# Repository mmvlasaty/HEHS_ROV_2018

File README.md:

# HEHS_ROV_2018

Control system repository for the HEHS 2018 MATE ROV competition team.

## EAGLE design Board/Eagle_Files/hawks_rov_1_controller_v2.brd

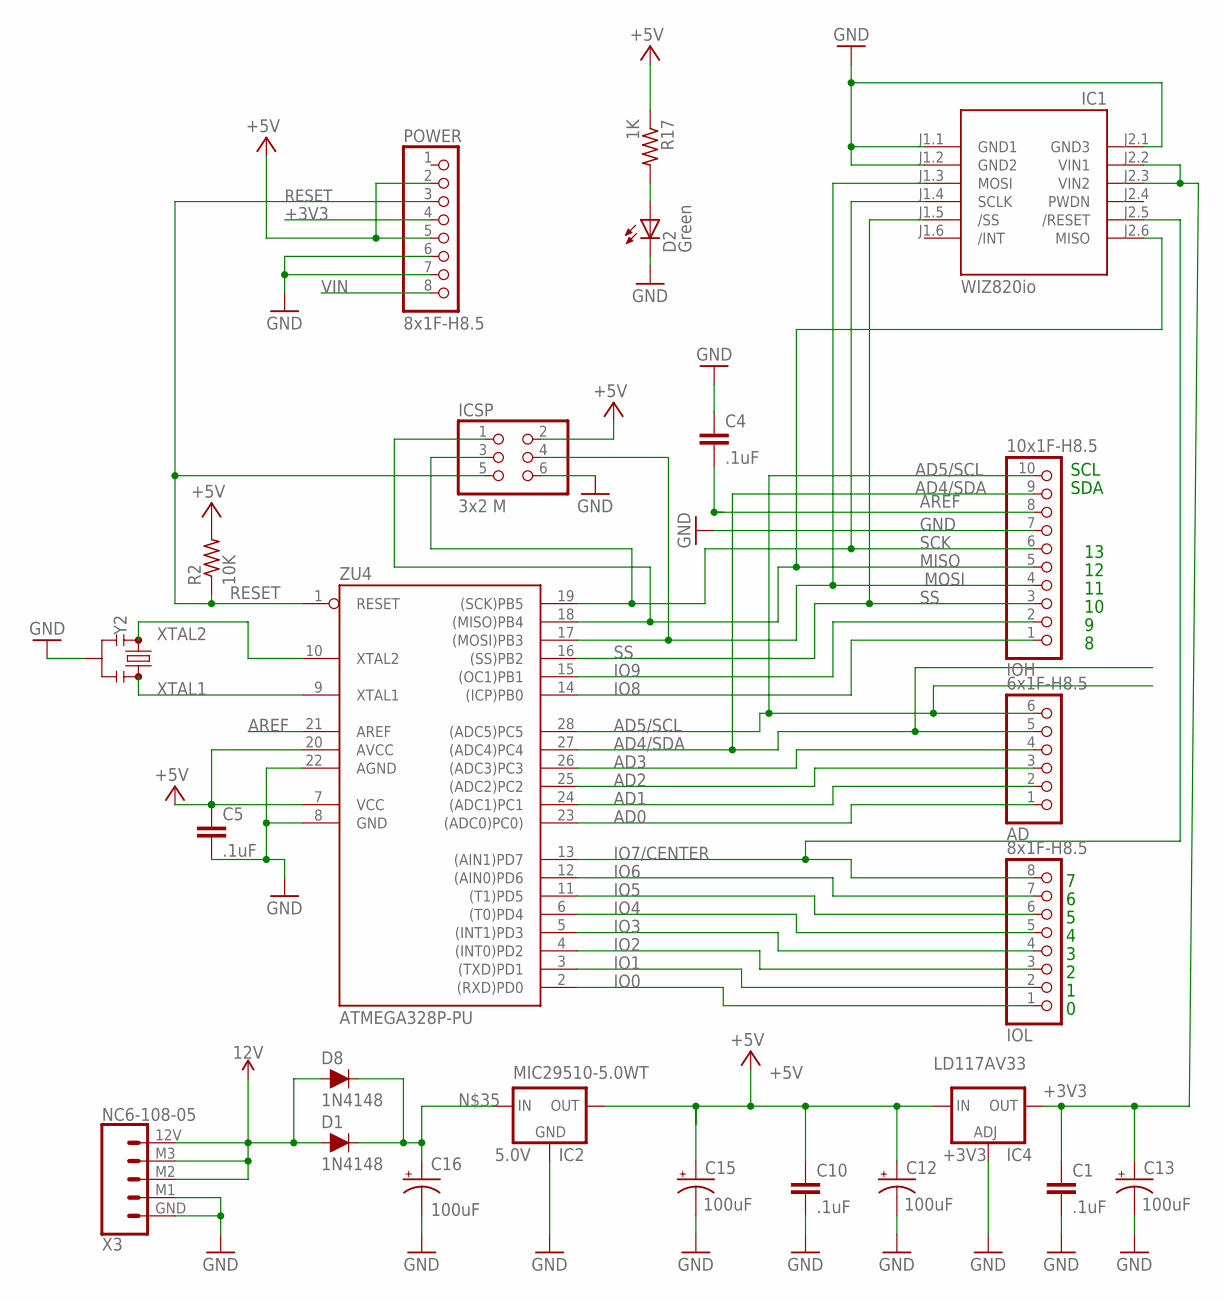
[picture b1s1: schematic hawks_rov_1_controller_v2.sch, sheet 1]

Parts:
AD: 6x1F-H8.5; 1X06
C1, C4, C5, C10: .1uF; CAP-PTH-5MM
C12, C13, C15, C16: 100uF; CPOL-RADIAL-2.5MM-5MM
D1, D8: 1N4148; DIODE-1N4148-KIT
D2: Green; LED3MM
IC1: WIZ820io; WIZ820IO
IC4: LD117AV33; TO220L1
ICSP: 3x2 M; 2X03
IOH: 10x1F-H8.5; 1X10
IOL: 8x1F-H8.5; 1X08
MIC29510-5.0WT: 5.0V; TO-220-STANDING
POWER: 8x1F-H8.5; 1X08
R2: 10K; 0207/10
R17: 1K; 0207/10
X3: NC6-108-05; SCREWTERMINAL-3.5MM-5
Y2: ZTT-16.00MX; SIP3-UA
ZU4: ATMEGA328P-PU; DIL28-3

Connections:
+3V3: C1.1, C13.1 (+), IC1.J2.2 (VIN1), IC1.J2.3 (VIN2), IC4.2 (OUT), POWER.4
+5V: C5.1, C10.1, C12.1 (+), C15.1 (+), IC4.3 (IN), ICSP.2, MIC29510-5.0WT.3 (OUT), POWER.2, POWER.5, R2.2, R17.1, ZU4.7 (VCC), ZU4.20 (AVCC); also elsewhere on the board
+12V: D1.A, D8.A, X3.12V (1), X3.M2 (3), X3.M3 (2)
AD0: AD.1, ZU4.23 ((ADC0)PC0))
AD1: AD.2, ZU4.24 ((ADC1)PC1)
AD2: AD.3, ZU4.25 ((ADC2)PC2)
AD3: AD.4, ZU4.26 ((ADC3)PC3)
AD4/SDA: AD.5, IOH.9, ZU4.27 ((ADC4)PC4); also elsewhere on the board
AD5/SCL: AD.6, IOH.10, ZU4.28 ((ADC5)PC5); also elsewhere on the board
AREF: C4.2, IOH.8, ZU4.21 (AREF)
GND: C1.2, C4.1, C5.2, C10.2, C12.2 (-), C13.2 (-), C15.2 (-), C16.2 (-), D2.K (C), IC1.J1.1 (GND1), IC1.J1.2 (GND2), IC1.J2.1 (GND3), IC4.1 (ADJ), ICSP.6, IOH.7, MIC29510-5.0WT.2 (GND), POWER.6, POWER.7, X3.GND (5), X3.M1 (4), Y2.2, ZU4.8 (GND), ZU4.22 (AGND); also elsewhere on the board
IO0: IOL.1, ZU4.2 ((RXD)PD0)
IO1: IOL.2, ZU4.3 ((TXD)PD1)
IO2: IOL.3, ZU4.4 ((INT0)PD2)
IO3: IOL.4, ZU4.5 ((INT1)PD3)
IO4: IOL.5, ZU4.6 ((T0)PD4)
IO5: IOL.6, ZU4.11 ((T1)PD5)
IO6: IOL.7, ZU4.12 ((AIN0)PD6)
IO7/CENTER: IC1.J2.5 (/RESET), IOL.8, ZU4.13 ((AIN1)PD7)
IO8: IOH.1, ZU4.14 ((ICP)PB0)
IO9: IOH.2, ZU4.15 ((OC1)PB1)
MISO: IC1.J2.6 (MISO), ICSP.1, IOH.5, ZU4.18 ((MISO)PB4)
MOSI: IC1.J1.3 (MOSI), ICSP.4, IOH.4, ZU4.17 ((MOSI)PB3)
unnamed: D2.A, R17.2
unnamed: C16.1 (+), D1.C, D8.C, MIC29510-5.0WT.1 (IN)
RESET: ICSP.5, POWER.3, R2.1, ZU4.1 (RESET)
SCK: IC1.J1.4 (SCLK), ICSP.3, IOH.6, ZU4.19 ((SCK)PB5)
SS: IC1.J1.5 (/SS), IOH.3, ZU4.16 ((SS)PB2)
VIN: POWER.8
XTAL1: Y2.3, ZU4.9 (XTAL1)
XTAL2: Y2.1, ZU4.10 (XTAL2)

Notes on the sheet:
SDA
SCL

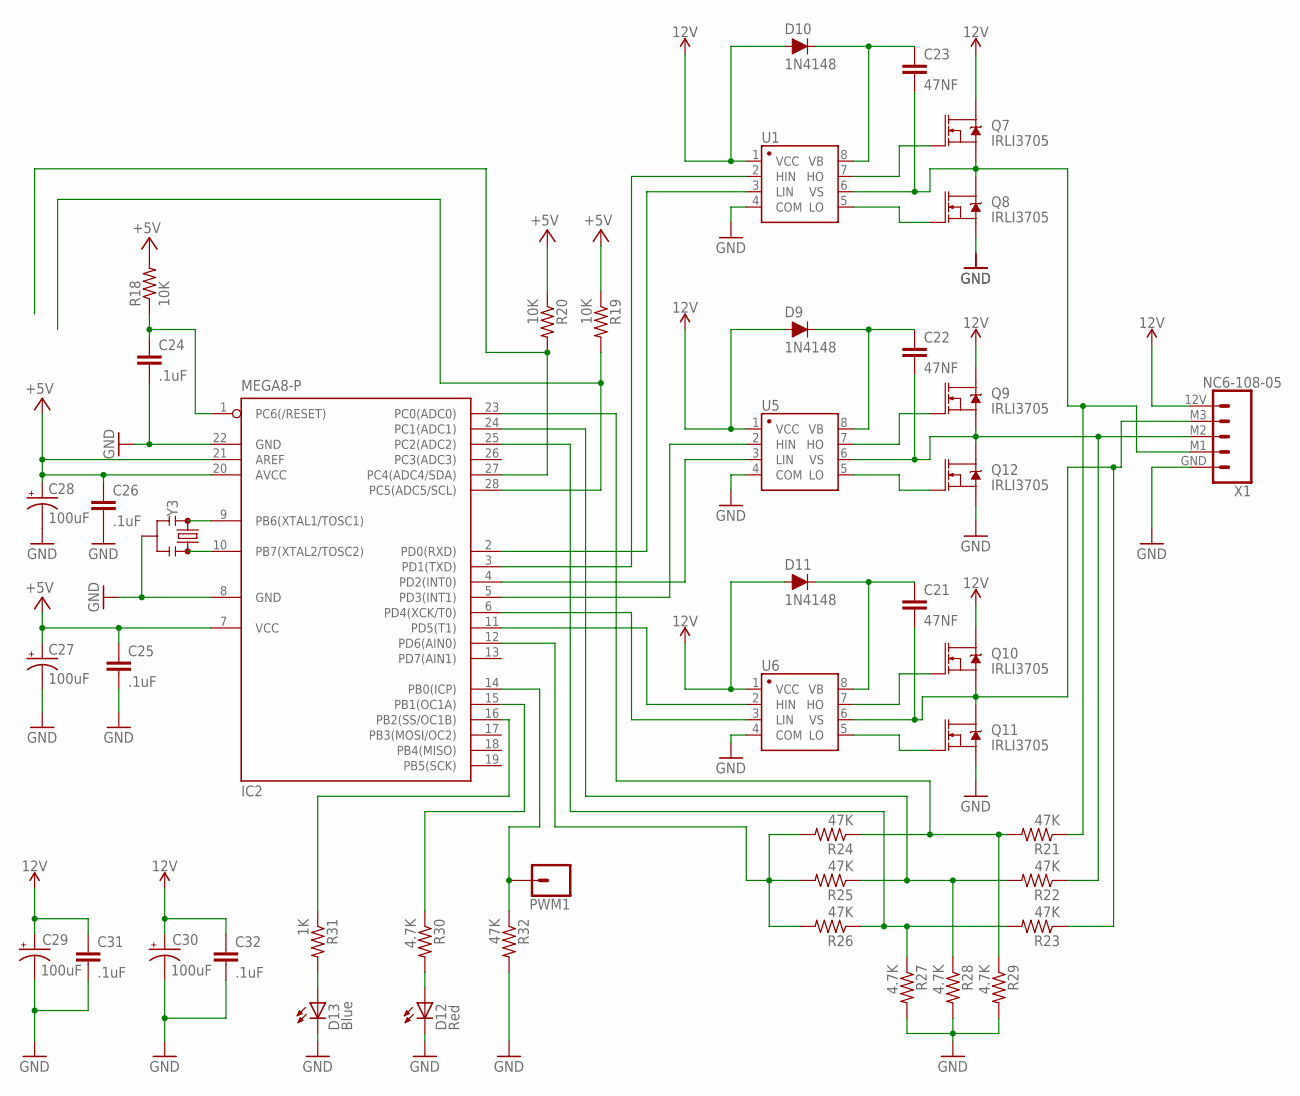
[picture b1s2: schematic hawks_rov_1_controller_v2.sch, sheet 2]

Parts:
C21, C22, C23: 47NF; CAP-PTH-5MM
C24, C25, C26, C31, C32: .1uF; CAP-PTH-5MM
C27, C28, C29, C30: 100uF; CPOL-RADIAL-2.5MM-5MM
D9, D10, D11: 1N4148; DIODE-1N4148-KIT
D12: Red; LED3MM
D13: Blue; LED3MM
IC2: MEGA8-P; DIL28-3
PWM1: CONN_01; 1X01
Q7, Q8, Q9, Q10, Q11, Q12: IRLI3705; TO220V
R18, R19, R20: 10K; 0207/10
R21, R22, R23, R24, R25, R26, R32: 47K; 0207/10
R27, R28, R29, R30: 4.7K; 0207/10
R31: 1K; 0207/10
U1, U5, U6: IR2101PBF; DIP-08
X1: NC6-108-05; SCREWTERMINAL-3.5MM-5
Y3: ZTT-16.00MX; SIP3-UA

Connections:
12V: C29.1 (+), C30.1 (+), C31.1, C32.1, D9.A, D10.A, D11.A, Q7.2 (D), Q9.2 (D), Q10.2 (D), U1.1 (VCC), U5.1 (VCC), U6.1 (VCC), X1.12V (1); also elsewhere on the board
+5V: C25.1, C26.1, C27.1 (+), C28.1 (+), IC2.7 (VCC), IC2.20 (AVCC), IC2.21 (AREF), R18.2, R19.1, R20.1; also elsewhere on the board
AD4/SDA: IC2.27 (PC4(ADC4/SDA)), R20.2; also elsewhere on the board
AD5/SCL: IC2.28 (PC5(ADC5/SCL)), R19.2; also elsewhere on the board
GND: C24.2, C25.2, C26.2, C27.2 (-), C28.2 (-), C29.2 (-), C30.2 (-), C31.2, C32.2, D12.K (C), D13.K (C), IC2.8 (GND), IC2.22 (GND), Q8.3 (S), Q11.3 (S), Q12.3 (S), R27.2, R28.2, R29.2, R32.2, U1.4 (COM), U5.4 (COM), U6.4 (COM), X1.GND (5), Y3.2; also elsewhere on the board
unnamed: IC2.3 (PD1(TXD)), U1.2 (HIN)
unnamed: IC2.2 (PD0(RXD)), U1.3 (LIN)
unnamed: IC2.5 (PD3(INT1)), U5.2 (HIN)
unnamed: IC2.4 (PD2(INT0)), U5.3 (LIN)
unnamed: IC2.11 (PD5(T1)), U6.2 (HIN)
unnamed: IC2.6 (PD4(XCK/T0)), U6.3 (LIN)
unnamed: Q7.1 (G), U1.7 (HO)
unnamed: Q8.1 (G), U1.5 (LO)
unnamed: Q9.1 (G), U5.7 (HO)
unnamed: Q12.1 (G), U5.5 (LO)
unnamed: Q10.1 (G), U6.7 (HO)
unnamed: Q11.1 (G), U6.5 (LO)
unnamed: C22.1, D9.C, U5.8 (VB)
unnamed: C23.1, D10.C, U1.8 (VB)
unnamed: C21.1, D11.C, U6.8 (VB)
unnamed: IC2.23 (PC0(ADC0)), R21.2, R24.1, R29.1
unnamed: IC2.24 (PC1(ADC1)), R22.2, R25.1, R28.1
unnamed: IC2.25 (PC2(ADC2)), R23.2, R26.1, R27.1
unnamed: C21.2, Q10.3 (S), Q11.2 (D), R23.1, U6.6 (VS), X1.M3 (2)
unnamed: C22.2, Q9.3 (S), Q12.2 (D), R22.1, U5.6 (VS), X1.M2 (3)
unnamed: C23.2, Q7.3 (S), Q8.2 (D), R21.1, U1.6 (VS), X1.M1 (4)
unnamed: IC2.12 (PD6(AIN0)), R24.2, R25.2, R26.2
unnamed: IC2.9 (PB6(XTAL1/TOSC1)), Y3.1
unnamed: IC2.10 (PB7(XTAL2/TOSC2)), Y3.3
unnamed: D12.A, R30.2
unnamed: D13.A, R31.2
unnamed: IC2.15 (PB1(OC1A)), R30.1
unnamed: IC2.16 (PB2(SS/OC1B)), R31.1
unnamed: C24.1, IC2.1 (PC6(/RESET)), R18.1
unnamed: IC2.14 (PB0(ICP)), PWM1.1, R32.1

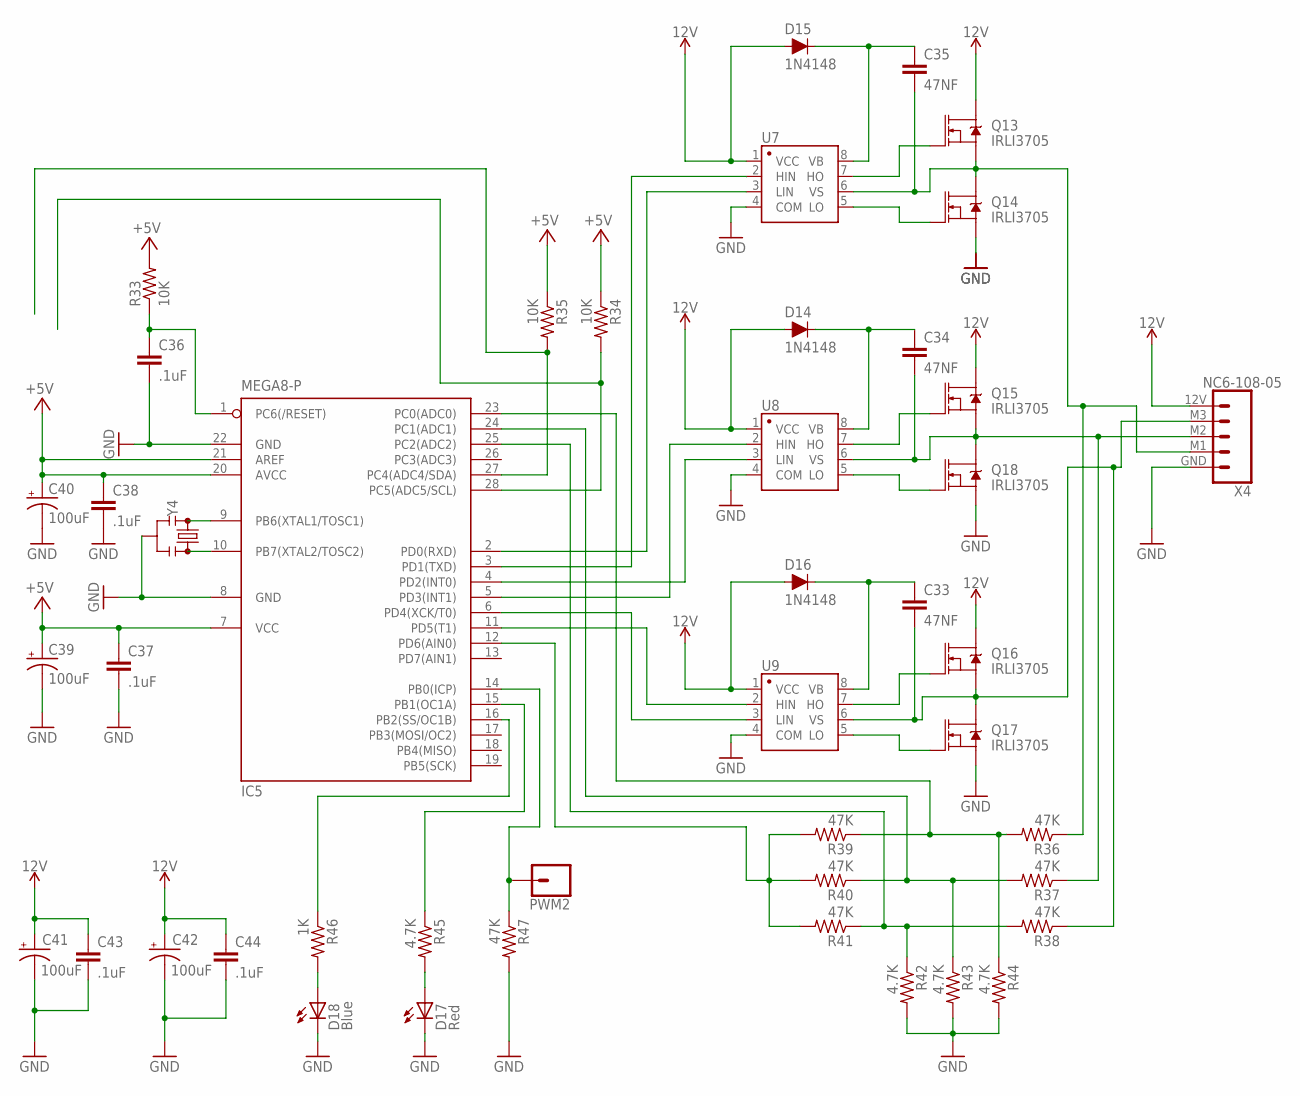
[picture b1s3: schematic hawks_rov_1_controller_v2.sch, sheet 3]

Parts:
C33, C34, C35: 47NF; CAP-PTH-5MM
C36, C37, C38, C43, C44: .1uF; CAP-PTH-5MM
C39, C40, C41, C42: 100uF; CPOL-RADIAL-2.5MM-5MM
D14, D15, D16: 1N4148; DIODE-1N4148-KIT
D17: Red; LED3MM
D18: Blue; LED3MM
IC5: MEGA8-P; DIL28-3
PWM2: CONN_01; 1X01
Q13, Q14, Q15, Q16, Q17, Q18: IRLI3705; TO220V
R33, R34, R35: 10K; 0207/10
R36, R37, R38, R39, R40, R41, R47: 47K; 0207/10
R42, R43, R44, R45: 4.7K; 0207/10
R46: 1K; 0207/10
U7, U8, U9: IR2101PBF; DIP-08
X4: NC6-108-05; SCREWTERMINAL-3.5MM-5
Y4: ZTT-16.00MX; SIP3-UA

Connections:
12V: C41.1 (+), C42.1 (+), C43.1, C44.1, D14.A, D15.A, D16.A, Q13.2 (D), Q15.2 (D), Q16.2 (D), U7.1 (VCC), U8.1 (VCC), U9.1 (VCC), X4.12V (1); also elsewhere on the board
+5V: C37.1, C38.1, C39.1 (+), C40.1 (+), IC5.7 (VCC), IC5.20 (AVCC), IC5.21 (AREF), R33.2, R34.1, R35.1; also elsewhere on the board
AD4/SDA: IC5.27 (PC4(ADC4/SDA)), R35.2; also elsewhere on the board
AD5/SCL: IC5.28 (PC5(ADC5/SCL)), R34.2; also elsewhere on the board
GND: C36.2, C37.2, C38.2, C39.2 (-), C40.2 (-), C41.2 (-), C42.2 (-), C43.2, C44.2, D17.K (C), D18.K (C), IC5.8 (GND), IC5.22 (GND), Q14.3 (S), Q17.3 (S), Q18.3 (S), R42.2, R43.2, R44.2, R47.2, U7.4 (COM), U8.4 (COM), U9.4 (COM), X4.GND (5), Y4.2; also elsewhere on the board
unnamed: IC5.3 (PD1(TXD)), U7.2 (HIN)
unnamed: IC5.2 (PD0(RXD)), U7.3 (LIN)
unnamed: IC5.5 (PD3(INT1)), U8.2 (HIN)
unnamed: IC5.4 (PD2(INT0)), U8.3 (LIN)
unnamed: IC5.11 (PD5(T1)), U9.2 (HIN)
unnamed: IC5.6 (PD4(XCK/T0)), U9.3 (LIN)
unnamed: Q13.1 (G), U7.7 (HO)
unnamed: Q14.1 (G), U7.5 (LO)
unnamed: Q15.1 (G), U8.7 (HO)
unnamed: Q18.1 (G), U8.5 (LO)
unnamed: Q16.1 (G), U9.7 (HO)
unnamed: Q17.1 (G), U9.5 (LO)
unnamed: C34.1, D14.C, U8.8 (VB)
unnamed: C35.1, D15.C, U7.8 (VB)
unnamed: C33.1, D16.C, U9.8 (VB)
unnamed: IC5.23 (PC0(ADC0)), R36.2, R39.1, R44.1
unnamed: IC5.24 (PC1(ADC1)), R37.2, R40.1, R43.1
unnamed: IC5.25 (PC2(ADC2)), R38.2, R41.1, R42.1
unnamed: C33.2, Q16.3 (S), Q17.2 (D), R38.1, U9.6 (VS), X4.M3 (2)
unnamed: C34.2, Q15.3 (S), Q18.2 (D), R37.1, U8.6 (VS), X4.M2 (3)
unnamed: C35.2, Q13.3 (S), Q14.2 (D), R36.1, U7.6 (VS), X4.M1 (4)
unnamed: IC5.12 (PD6(AIN0)), R39.2, R40.2, R41.2
unnamed: IC5.9 (PB6(XTAL1/TOSC1)), Y4.1
unnamed: IC5.10 (PB7(XTAL2/TOSC2)), Y4.3
unnamed: D17.A, R45.2
unnamed: D18.A, R46.2
unnamed: IC5.15 (PB1(OC1A)), R45.1
unnamed: IC5.16 (PB2(SS/OC1B)), R46.1
unnamed: C36.1, IC5.1 (PC6(/RESET)), R33.1
unnamed: IC5.14 (PB0(ICP)), PWM2.1, R47.1

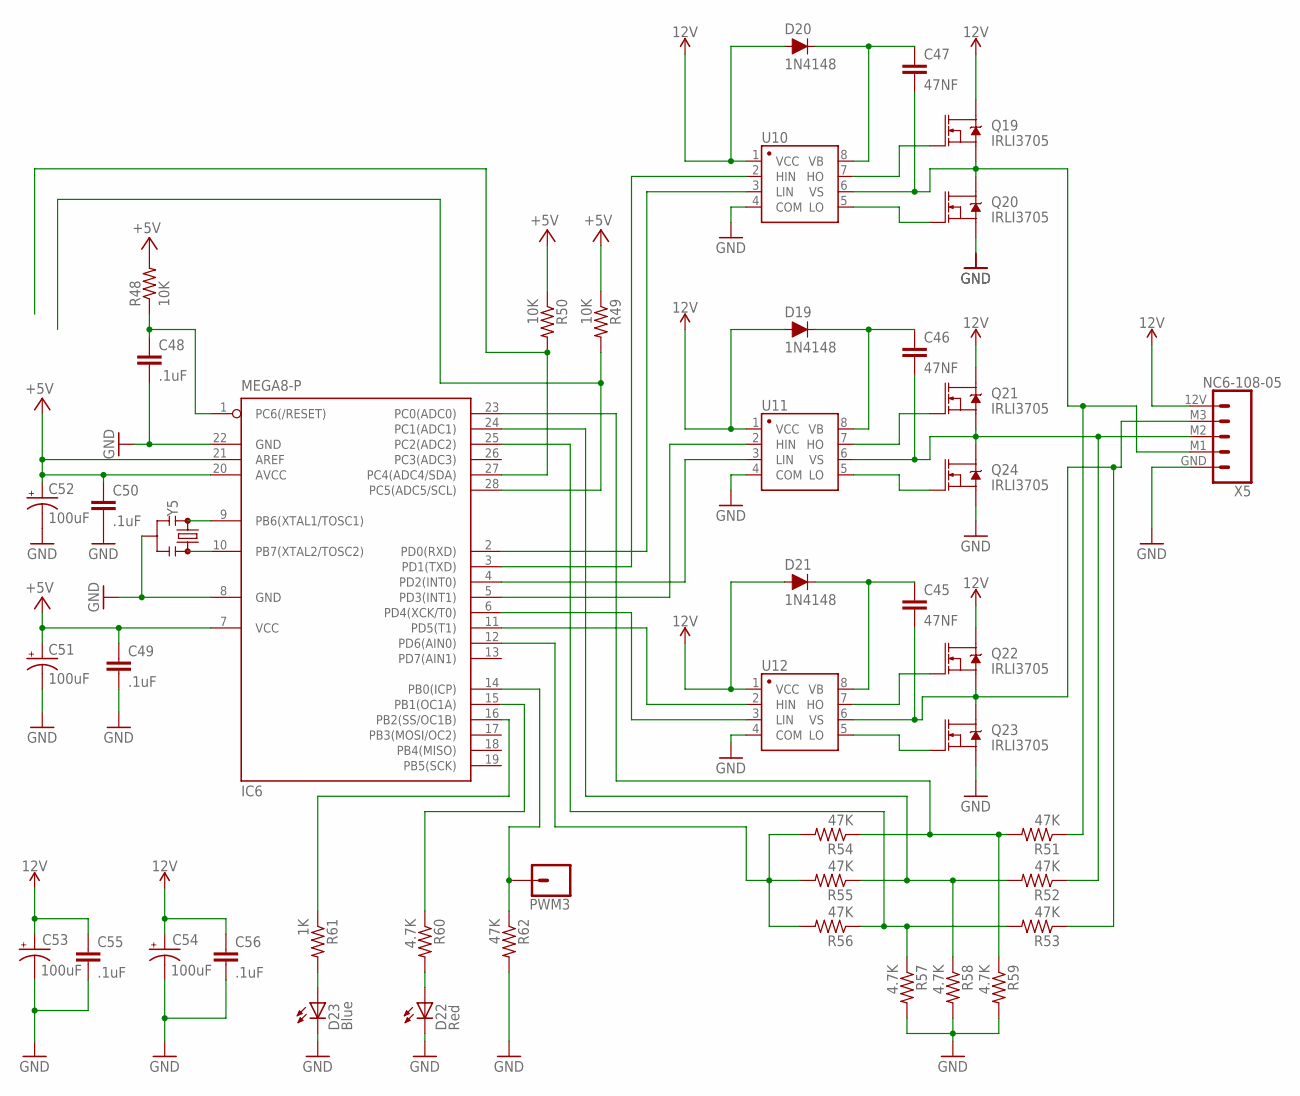
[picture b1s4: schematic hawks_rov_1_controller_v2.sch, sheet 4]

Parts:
C45, C46, C47: 47NF; CAP-PTH-5MM
C48, C49, C50, C55, C56: .1uF; CAP-PTH-5MM
C51, C52, C53, C54: 100uF; CPOL-RADIAL-2.5MM-5MM
D19, D20, D21: 1N4148; DIODE-1N4148-KIT
D22: Red; LED3MM
D23: Blue; LED3MM
IC6: MEGA8-P; DIL28-3
PWM3: CONN_01; 1X01
Q19, Q20, Q21, Q22, Q23, Q24: IRLI3705; TO220V
R48, R49, R50: 10K; 0207/10
R51, R52, R53, R54, R55, R56, R62: 47K; 0207/10
R57, R58, R59, R60: 4.7K; 0207/10
R61: 1K; 0207/10
U10, U11, U12: IR2101PBF; DIP-08
X5: NC6-108-05; SCREWTERMINAL-3.5MM-5
Y5: ZTT-16.00MX; SIP3-UA

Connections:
12V: C53.1 (+), C54.1 (+), C55.1, C56.1, D19.A, D20.A, D21.A, Q19.2 (D), Q21.2 (D), Q22.2 (D), U10.1 (VCC), U11.1 (VCC), U12.1 (VCC), X5.12V (1); also elsewhere on the board
+5V: C49.1, C50.1, C51.1 (+), C52.1 (+), IC6.7 (VCC), IC6.20 (AVCC), IC6.21 (AREF), R48.2, R49.1, R50.1; also elsewhere on the board
AD4/SDA: IC6.27 (PC4(ADC4/SDA)), R50.2; also elsewhere on the board
AD5/SCL: IC6.28 (PC5(ADC5/SCL)), R49.2; also elsewhere on the board
GND: C48.2, C49.2, C50.2, C51.2 (-), C52.2 (-), C53.2 (-), C54.2 (-), C55.2, C56.2, D22.K (C), D23.K (C), IC6.8 (GND), IC6.22 (GND), Q20.3 (S), Q23.3 (S), Q24.3 (S), R57.2, R58.2, R59.2, R62.2, U10.4 (COM), U11.4 (COM), U12.4 (COM), X5.GND (5), Y5.2; also elsewhere on the board
unnamed: IC6.3 (PD1(TXD)), U10.2 (HIN)
unnamed: IC6.2 (PD0(RXD)), U10.3 (LIN)
unnamed: IC6.5 (PD3(INT1)), U11.2 (HIN)
unnamed: IC6.4 (PD2(INT0)), U11.3 (LIN)
unnamed: IC6.11 (PD5(T1)), U12.2 (HIN)
unnamed: IC6.6 (PD4(XCK/T0)), U12.3 (LIN)
unnamed: Q19.1 (G), U10.7 (HO)
unnamed: Q20.1 (G), U10.5 (LO)
unnamed: Q21.1 (G), U11.7 (HO)
unnamed: Q24.1 (G), U11.5 (LO)
unnamed: Q22.1 (G), U12.7 (HO)
unnamed: Q23.1 (G), U12.5 (LO)
unnamed: C46.1, D19.C, U11.8 (VB)
unnamed: C47.1, D20.C, U10.8 (VB)
unnamed: C45.1, D21.C, U12.8 (VB)
unnamed: IC6.23 (PC0(ADC0)), R51.2, R54.1, R59.1
unnamed: IC6.24 (PC1(ADC1)), R52.2, R55.1, R58.1
unnamed: IC6.25 (PC2(ADC2)), R53.2, R56.1, R57.1
unnamed: C45.2, Q22.3 (S), Q23.2 (D), R53.1, U12.6 (VS), X5.M3 (2)
unnamed: C46.2, Q21.3 (S), Q24.2 (D), R52.1, U11.6 (VS), X5.M2 (3)
unnamed: C47.2, Q19.3 (S), Q20.2 (D), R51.1, U10.6 (VS), X5.M1 (4)
unnamed: IC6.12 (PD6(AIN0)), R54.2, R55.2, R56.2
unnamed: IC6.9 (PB6(XTAL1/TOSC1)), Y5.1
unnamed: IC6.10 (PB7(XTAL2/TOSC2)), Y5.3
unnamed: D22.A, R60.2
unnamed: D23.A, R61.2
unnamed: IC6.15 (PB1(OC1A)), R60.1
unnamed: IC6.16 (PB2(SS/OC1B)), R61.1
unnamed: C48.1, IC6.1 (PC6(/RESET)), R48.1
unnamed: IC6.14 (PB0(ICP)), PWM3.1, R62.1

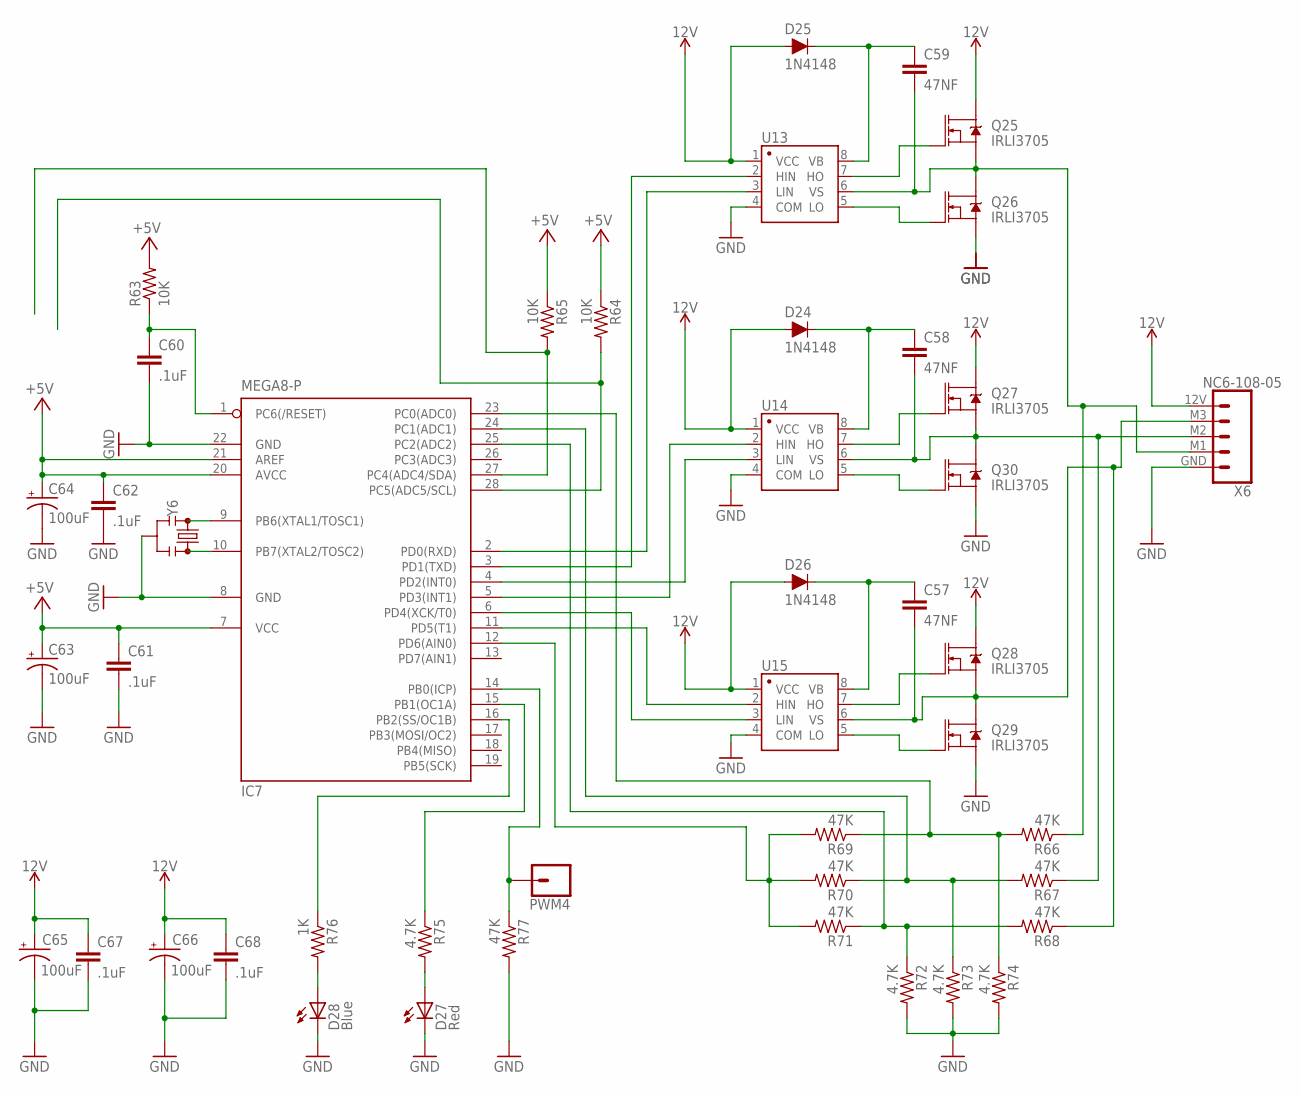
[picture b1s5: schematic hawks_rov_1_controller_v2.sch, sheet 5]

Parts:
C57, C58, C59: 47NF; CAP-PTH-5MM
C60, C61, C62, C67, C68: .1uF; CAP-PTH-5MM
C63, C64, C65, C66: 100uF; CPOL-RADIAL-2.5MM-5MM
D24, D25, D26: 1N4148; DIODE-1N4148-KIT
D27: Red; LED3MM
D28: Blue; LED3MM
IC7: MEGA8-P; DIL28-3
PWM4: CONN_01; 1X01
Q25, Q26, Q27, Q28, Q29, Q30: IRLI3705; TO220V
R63, R64, R65: 10K; 0207/10
R66, R67, R68, R69, R70, R71, R77: 47K; 0207/10
R72, R73, R74, R75: 4.7K; 0207/10
R76: 1K; 0207/10
U13, U14, U15: IR2101PBF; DIP-08
X6: NC6-108-05; SCREWTERMINAL-3.5MM-5
Y6: ZTT-16.00MX; SIP3-UA

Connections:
12V: C65.1 (+), C66.1 (+), C67.1, C68.1, D24.A, D25.A, D26.A, Q25.2 (D), Q27.2 (D), Q28.2 (D), U13.1 (VCC), U14.1 (VCC), U15.1 (VCC), X6.12V (1); also elsewhere on the board
+5V: C61.1, C62.1, C63.1 (+), C64.1 (+), IC7.7 (VCC), IC7.20 (AVCC), IC7.21 (AREF), R63.2, R64.1, R65.1; also elsewhere on the board
AD4/SDA: IC7.27 (PC4(ADC4/SDA)), R65.2; also elsewhere on the board
AD5/SCL: IC7.28 (PC5(ADC5/SCL)), R64.2; also elsewhere on the board
GND: C60.2, C61.2, C62.2, C63.2 (-), C64.2 (-), C65.2 (-), C66.2 (-), C67.2, C68.2, D27.K (C), D28.K (C), IC7.8 (GND), IC7.22 (GND), Q26.3 (S), Q29.3 (S), Q30.3 (S), R72.2, R73.2, R74.2, R77.2, U13.4 (COM), U14.4 (COM), U15.4 (COM), X6.GND (5), Y6.2; also elsewhere on the board
unnamed: IC7.3 (PD1(TXD)), U13.2 (HIN)
unnamed: IC7.2 (PD0(RXD)), U13.3 (LIN)
unnamed: IC7.5 (PD3(INT1)), U14.2 (HIN)
unnamed: IC7.4 (PD2(INT0)), U14.3 (LIN)
unnamed: IC7.11 (PD5(T1)), U15.2 (HIN)
unnamed: IC7.6 (PD4(XCK/T0)), U15.3 (LIN)
unnamed: Q25.1 (G), U13.7 (HO)
unnamed: Q26.1 (G), U13.5 (LO)
unnamed: Q27.1 (G), U14.7 (HO)
unnamed: Q30.1 (G), U14.5 (LO)
unnamed: Q28.1 (G), U15.7 (HO)
unnamed: Q29.1 (G), U15.5 (LO)
unnamed: C58.1, D24.C, U14.8 (VB)
unnamed: C59.1, D25.C, U13.8 (VB)
unnamed: C57.1, D26.C, U15.8 (VB)
unnamed: IC7.23 (PC0(ADC0)), R66.2, R69.1, R74.1
unnamed: IC7.24 (PC1(ADC1)), R67.2, R70.1, R73.1
unnamed: IC7.25 (PC2(ADC2)), R68.2, R71.1, R72.1
unnamed: C57.2, Q28.3 (S), Q29.2 (D), R68.1, U15.6 (VS), X6.M3 (2)
unnamed: C58.2, Q27.3 (S), Q30.2 (D), R67.1, U14.6 (VS), X6.M2 (3)
unnamed: C59.2, Q25.3 (S), Q26.2 (D), R66.1, U13.6 (VS), X6.M1 (4)
unnamed: IC7.12 (PD6(AIN0)), R69.2, R70.2, R71.2
unnamed: IC7.9 (PB6(XTAL1/TOSC1)), Y6.1
unnamed: IC7.10 (PB7(XTAL2/TOSC2)), Y6.3
unnamed: D27.A, R75.2
unnamed: D28.A, R76.2
unnamed: IC7.15 (PB1(OC1A)), R75.1
unnamed: IC7.16 (PB2(SS/OC1B)), R76.1
unnamed: C60.1, IC7.1 (PC6(/RESET)), R63.1
unnamed: IC7.14 (PB0(ICP)), PWM4.1, R77.1

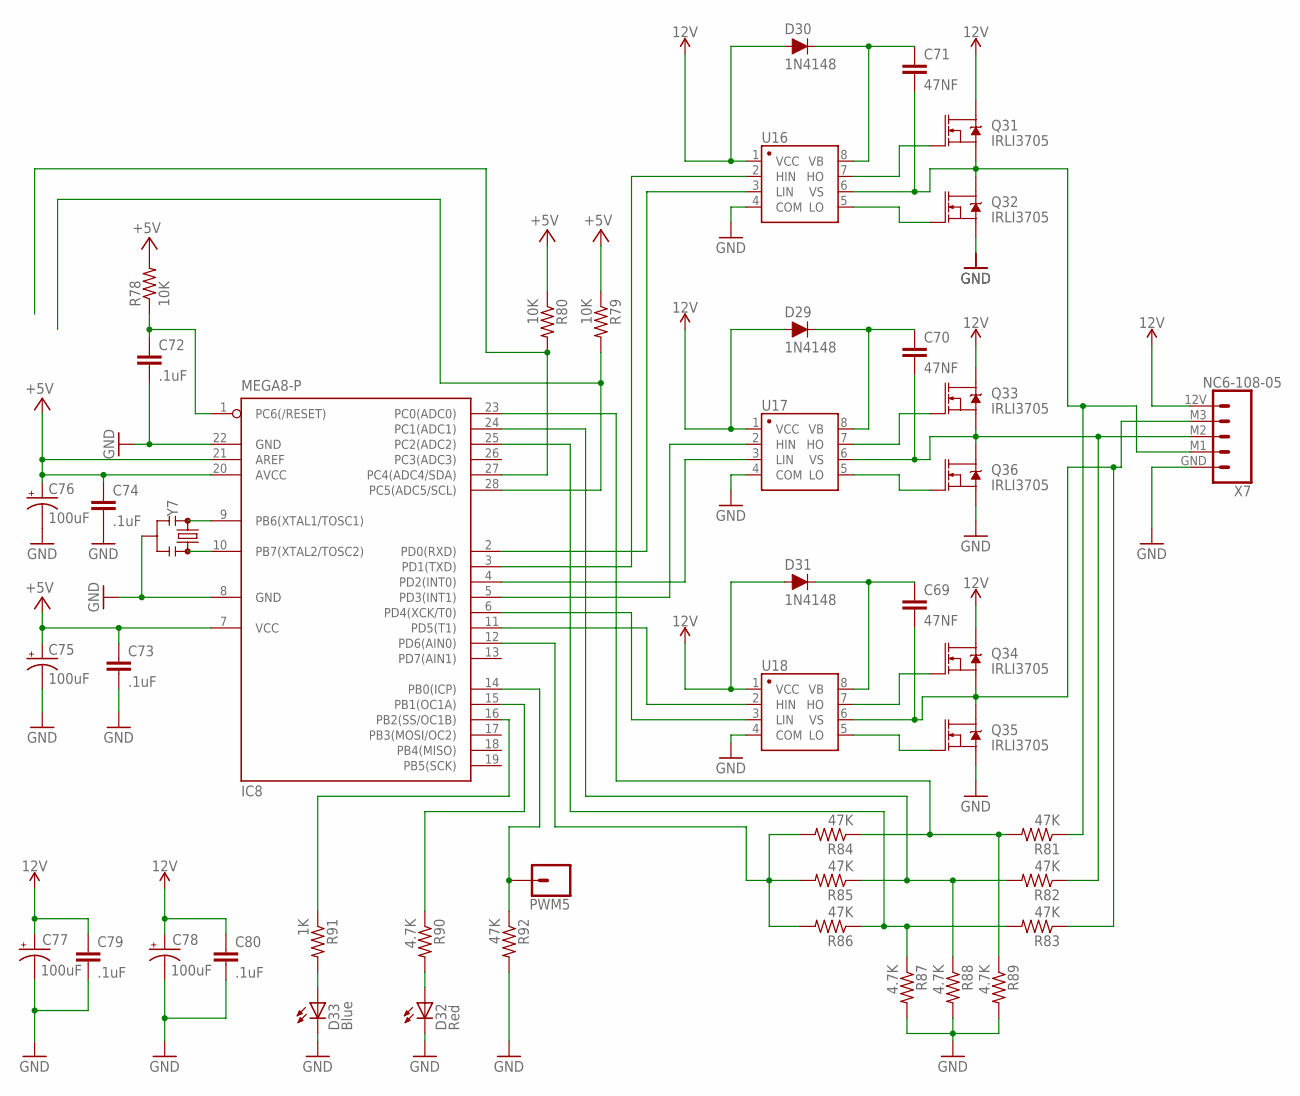
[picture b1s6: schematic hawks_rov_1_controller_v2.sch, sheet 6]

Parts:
C69, C70, C71: 47NF; CAP-PTH-5MM
C72, C73, C74, C79, C80: .1uF; CAP-PTH-5MM
C75, C76, C77, C78: 100uF; CPOL-RADIAL-2.5MM-5MM
D29, D30, D31: 1N4148; DIODE-1N4148-KIT
D32: Red; LED3MM
D33: Blue; LED3MM
IC8: MEGA8-P; DIL28-3
PWM5: CONN_01; 1X01
Q31, Q32, Q33, Q34, Q35, Q36: IRLI3705; TO220V
R78, R79, R80: 10K; 0207/10
R81, R82, R83, R84, R85, R86, R92: 47K; 0207/10
R87, R88, R89, R90: 4.7K; 0207/10
R91: 1K; 0207/10
U16, U17, U18: IR2101PBF; DIP-08
X7: NC6-108-05; SCREWTERMINAL-3.5MM-5
Y7: ZTT-16.00MX; SIP3-UA

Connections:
12V: C77.1 (+), C78.1 (+), C79.1, C80.1, D29.A, D30.A, D31.A, Q31.2 (D), Q33.2 (D), Q34.2 (D), U16.1 (VCC), U17.1 (VCC), U18.1 (VCC), X7.12V (1); also elsewhere on the board
+5V: C73.1, C74.1, C75.1 (+), C76.1 (+), IC8.7 (VCC), IC8.20 (AVCC), IC8.21 (AREF), R78.2, R79.1, R80.1; also elsewhere on the board
AD4/SDA: IC8.27 (PC4(ADC4/SDA)), R80.2; also elsewhere on the board
AD5/SCL: IC8.28 (PC5(ADC5/SCL)), R79.2; also elsewhere on the board
GND: C72.2, C73.2, C74.2, C75.2 (-), C76.2 (-), C77.2 (-), C78.2 (-), C79.2, C80.2, D32.K (C), D33.K (C), IC8.8 (GND), IC8.22 (GND), Q32.3 (S), Q35.3 (S), Q36.3 (S), R87.2, R88.2, R89.2, R92.2, U16.4 (COM), U17.4 (COM), U18.4 (COM), X7.GND (5), Y7.2; also elsewhere on the board
unnamed: IC8.3 (PD1(TXD)), U16.2 (HIN)
unnamed: IC8.2 (PD0(RXD)), U16.3 (LIN)
unnamed: IC8.5 (PD3(INT1)), U17.2 (HIN)
unnamed: IC8.4 (PD2(INT0)), U17.3 (LIN)
unnamed: IC8.11 (PD5(T1)), U18.2 (HIN)
unnamed: IC8.6 (PD4(XCK/T0)), U18.3 (LIN)
unnamed: Q31.1 (G), U16.7 (HO)
unnamed: Q32.1 (G), U16.5 (LO)
unnamed: Q33.1 (G), U17.7 (HO)
unnamed: Q36.1 (G), U17.5 (LO)
unnamed: Q34.1 (G), U18.7 (HO)
unnamed: Q35.1 (G), U18.5 (LO)
unnamed: C70.1, D29.C, U17.8 (VB)
unnamed: C71.1, D30.C, U16.8 (VB)
unnamed: C69.1, D31.C, U18.8 (VB)
unnamed: IC8.23 (PC0(ADC0)), R81.2, R84.1, R89.1
unnamed: IC8.24 (PC1(ADC1)), R82.2, R85.1, R88.1
unnamed: IC8.25 (PC2(ADC2)), R83.2, R86.1, R87.1
unnamed: C69.2, Q34.3 (S), Q35.2 (D), R83.1, U18.6 (VS), X7.M3 (2)
unnamed: C70.2, Q33.3 (S), Q36.2 (D), R82.1, U17.6 (VS), X7.M2 (3)
unnamed: C71.2, Q31.3 (S), Q32.2 (D), R81.1, U16.6 (VS), X7.M1 (4)
unnamed: IC8.12 (PD6(AIN0)), R84.2, R85.2, R86.2
unnamed: IC8.9 (PB6(XTAL1/TOSC1)), Y7.1
unnamed: IC8.10 (PB7(XTAL2/TOSC2)), Y7.3
unnamed: D32.A, R90.2
unnamed: D33.A, R91.2
unnamed: IC8.15 (PB1(OC1A)), R90.1
unnamed: IC8.16 (PB2(SS/OC1B)), R91.1
unnamed: C72.1, IC8.1 (PC6(/RESET)), R78.1
unnamed: IC8.14 (PB0(ICP)), PWM5.1, R92.1

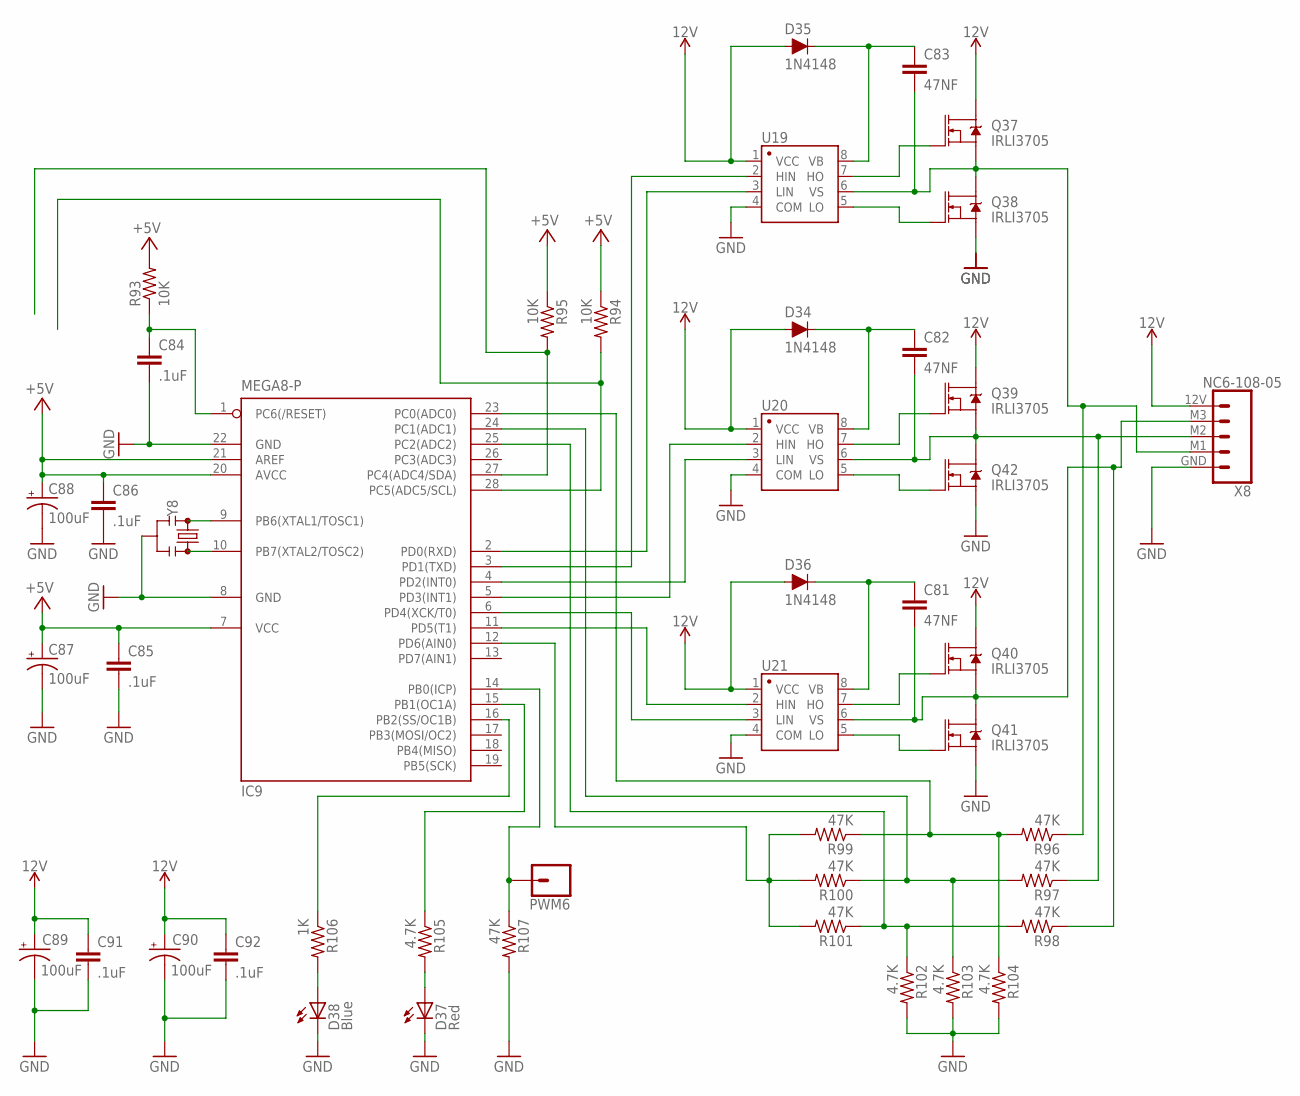
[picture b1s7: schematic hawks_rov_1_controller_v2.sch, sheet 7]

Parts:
C81, C82, C83: 47NF; CAP-PTH-5MM
C84, C85, C86, C91, C92: .1uF; CAP-PTH-5MM
C87, C88, C89, C90: 100uF; CPOL-RADIAL-2.5MM-5MM
D34, D35, D36: 1N4148; DIODE-1N4148-KIT
D37: Red; LED3MM
D38: Blue; LED3MM
IC9: MEGA8-P; DIL28-3
PWM6: CONN_01; 1X01
Q37, Q38, Q39, Q40, Q41, Q42: IRLI3705; TO220V
R93, R94, R95: 10K; 0207/10
R96, R97, R98, R99, R100, R101, R107: 47K; 0207/10
R102, R103, R104, R105: 4.7K; 0207/10
R106: 1K; 0207/10
U19, U20, U21: IR2101PBF; DIP-08
X8: NC6-108-05; SCREWTERMINAL-3.5MM-5
Y8: ZTT-16.00MX; SIP3-UA

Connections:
12V: C89.1 (+), C90.1 (+), C91.1, C92.1, D34.A, D35.A, D36.A, Q37.2 (D), Q39.2 (D), Q40.2 (D), U19.1 (VCC), U20.1 (VCC), U21.1 (VCC), X8.12V (1); also elsewhere on the board
+5V: C85.1, C86.1, C87.1 (+), C88.1 (+), IC9.7 (VCC), IC9.20 (AVCC), IC9.21 (AREF), R93.2, R94.1, R95.1; also elsewhere on the board
AD4/SDA: IC9.27 (PC4(ADC4/SDA)), R95.2; also elsewhere on the board
AD5/SCL: IC9.28 (PC5(ADC5/SCL)), R94.2; also elsewhere on the board
GND: C84.2, C85.2, C86.2, C87.2 (-), C88.2 (-), C89.2 (-), C90.2 (-), C91.2, C92.2, D37.K (C), D38.K (C), IC9.8 (GND), IC9.22 (GND), Q38.3 (S), Q41.3 (S), Q42.3 (S), R102.2, R103.2, R104.2, R107.2, U19.4 (COM), U20.4 (COM), U21.4 (COM), X8.GND (5), Y8.2; also elsewhere on the board
unnamed: IC9.3 (PD1(TXD)), U19.2 (HIN)
unnamed: IC9.2 (PD0(RXD)), U19.3 (LIN)
unnamed: IC9.5 (PD3(INT1)), U20.2 (HIN)
unnamed: IC9.4 (PD2(INT0)), U20.3 (LIN)
unnamed: IC9.11 (PD5(T1)), U21.2 (HIN)
unnamed: IC9.6 (PD4(XCK/T0)), U21.3 (LIN)
unnamed: Q37.1 (G), U19.7 (HO)
unnamed: Q38.1 (G), U19.5 (LO)
unnamed: Q39.1 (G), U20.7 (HO)
unnamed: Q42.1 (G), U20.5 (LO)
unnamed: Q40.1 (G), U21.7 (HO)
unnamed: Q41.1 (G), U21.5 (LO)
unnamed: C82.1, D34.C, U20.8 (VB)
unnamed: C83.1, D35.C, U19.8 (VB)
unnamed: C81.1, D36.C, U21.8 (VB)
unnamed: IC9.23 (PC0(ADC0)), R96.2, R99.1, R104.1
unnamed: IC9.24 (PC1(ADC1)), R97.2, R100.1, R103.1
unnamed: IC9.25 (PC2(ADC2)), R98.2, R101.1, R102.1
unnamed: C81.2, Q40.3 (S), Q41.2 (D), R98.1, U21.6 (VS), X8.M3 (2)
unnamed: C82.2, Q39.3 (S), Q42.2 (D), R97.1, U20.6 (VS), X8.M2 (3)
unnamed: C83.2, Q37.3 (S), Q38.2 (D), R96.1, U19.6 (VS), X8.M1 (4)
unnamed: IC9.12 (PD6(AIN0)), R99.2, R100.2, R101.2
unnamed: IC9.9 (PB6(XTAL1/TOSC1)), Y8.1
unnamed: IC9.10 (PB7(XTAL2/TOSC2)), Y8.3
unnamed: D37.A, R105.2
unnamed: D38.A, R106.2
unnamed: IC9.15 (PB1(OC1A)), R105.1
unnamed: IC9.16 (PB2(SS/OC1B)), R106.1
unnamed: C84.1, IC9.1 (PC6(/RESET)), R93.1
unnamed: IC9.14 (PB0(ICP)), PWM6.1, R107.1

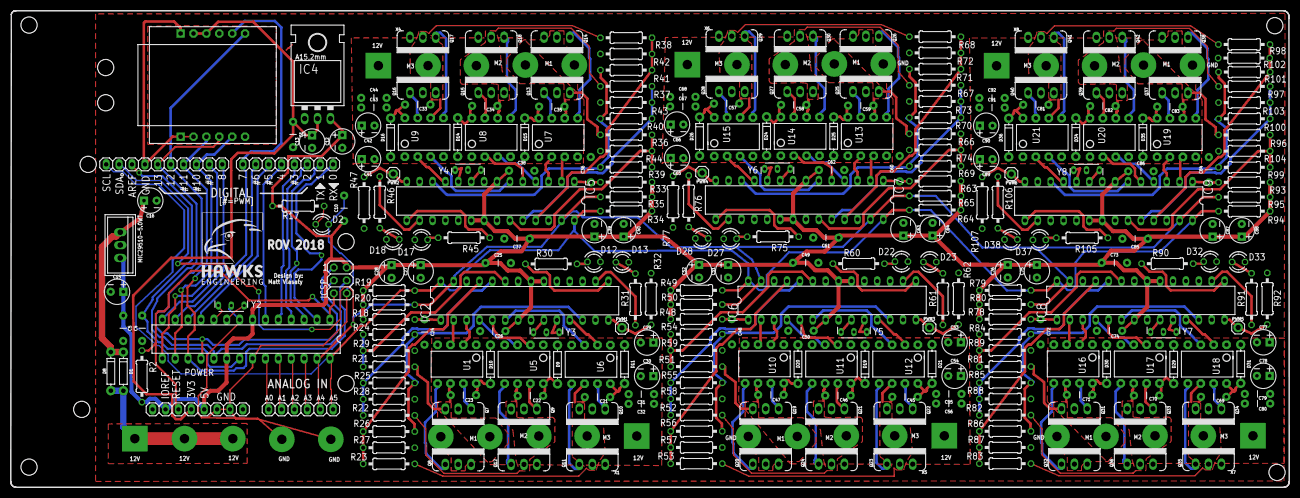
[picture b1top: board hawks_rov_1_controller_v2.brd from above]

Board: 2 copper layers, 251.8 x 93.9 mm, 295 parts (1 on the bottom side), 211 nets.

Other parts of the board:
U$1: IMAGE1#JPEG

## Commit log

2018-12-30 Edited readme
2018-12-30 Added board folder
2018-12-30 Added ESC firmware
2018-12-30 Added final control program
2018-12-30 Added setup instructions
2018-12-30 Added test programs
2018-12-30 Added Firmata
2018-12-30 Added Ethernet library
2018-12-30 Stopped ignoring .hex and .obj files
2018-12-30 Added ESC instructions
2018-12-30 PDF for ESC
2018-12-30 Added Firmata instructions
2019-01-01 Added control system explanation
2019-03-20 Added the modified Firmata files

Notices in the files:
parts and their libraries:
SparkFun-Capacitors: Licensing: Creative Commons ShareAlike 4.0 International - https://creativecommons.org/licenses/by-sa/4.0
